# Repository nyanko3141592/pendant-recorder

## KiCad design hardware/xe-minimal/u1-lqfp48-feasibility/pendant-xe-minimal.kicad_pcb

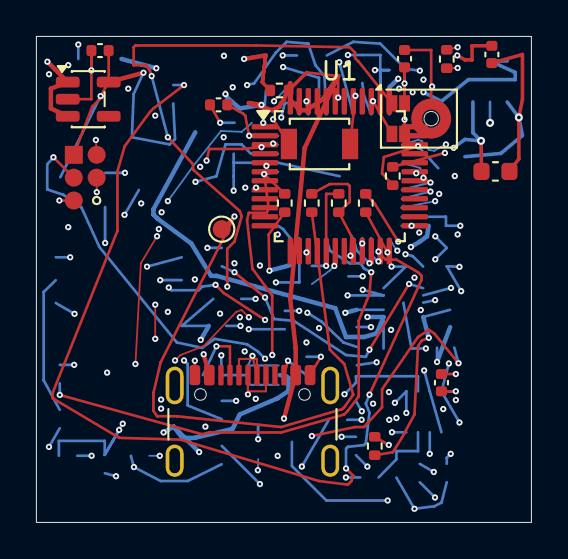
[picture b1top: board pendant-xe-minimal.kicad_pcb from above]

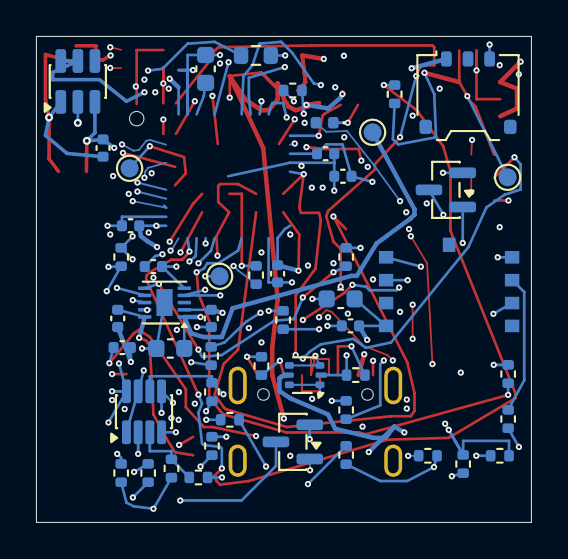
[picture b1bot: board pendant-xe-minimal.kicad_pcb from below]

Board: 6 copper layers, 27.5 x 27.0 mm, 71 parts (50 on the bottom side), 42 nets.

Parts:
C1, C2, C3, C6, C9, C22, C26: 100n; C_0402_1005Metric
C4: 10u; C_0603_1608Metric
C5: 4.7u; C_0603_1608Metric
C7, C16, C25: 1u; C_0402_1005Metric
C13: 2.2u 10V; C_0402_1005Metric
C14: 2.2u; C_0402_1005Metric
C15: 10u 10V effective >=1u; C_0603_1608Metric
C27: 4.7u effective TBD; C_0603_1608Metric
C28: 10n; C_0402_1005Metric
C29: 100n 10V; C_0402_1005Metric
C30: 50p 50V C0G; C_0402_1005Metric
D6: TJ-S1005SW4TGLC9Y-A5 amber LED; LED_0402_1005Metric
J1: USB4105-GF-A (candidate); USB_C_GCT_USB4105_GroundLand112
J2: Molex781710003 / DTP401525-XE; Molex_Pico-EZmate_78171-0003_1x03-1MP_P1.20mm_Vertical
J3: Factory SWD pogo candidate; SWD_Pogo_5Pad_P1.27mm
Q3, Q4: DMN63D8L-7; SOT-23
R1: 0R; R_0402_1005Metric
R2: 10k; R_0402_1005Metric
R3, R4, R13, R15, R22: 100k; R_0402_1005Metric
R6, R7: 5.1k 1%; R_0402_1005Metric
R10: 6.8k 1%; R_0402_1005Metric
R11, R39: 20k 1%; R_0402_1005Metric
R12, R36, R37, R38, R40: 100k 1%; R_0402_1005Metric
R14: 1M; R_0402_1005Metric
R21, R23: 22R tentative; R_0402_1005Metric
R24, R25, R28: 47k; R_0402_1005Metric
R32: 6.8k tentative; R_0402_1005Metric
R33, R34: 1M 1%; R_0402_1005Metric
R35: 10k 1%; R_0402_1005Metric
R41: 7.5k 1%; R_0402_1005Metric
R42: PTFR0402B24K0P9 24k 0.1%; R_0402_1005Metric
R43: 4.7k 1%; R_0402_1005Metric
R51: 0R 1%; R_0402_1005Metric
SW1: B3U-1000P (candidate); SW_SPST_B3U-1000P
TH1: NCU18XH103F60RB 10k 1% B3380; R_0603_1608Metric
TP1, TP2, TP3, TP5, TP6: TestPoint; TestPoint_Pad_D1.0mm
U1: STM32U585CIT6; LQFP-48_7x7mm_P0.5mm
U2: USBLC6-2P6; SOT-666
U3: BQ25185DLHR; Texas_DLH0010A_WSON-10-1EP_2.2x2mm_P0.4mm_EP0.9x1.5mm
U4: TPS7A0233PDBVR; SOT-23-5
U8: IM69D130V01; IM69D130_JLC_SMD_trial
U10: TPS22917DBVT; SOT-23-6
U11: CSNP32GCR01-BOW candidate; CSNP32GCR01_LGA8
U12: TLV7042DDFR; SOT-23-8

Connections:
/BAT: C14.1, J2.1, R33.1, TP1.1, U3.2
/BAT_ADC: C28.1, R33.2, R34.1, U1.11
/BAT_TS: R37.2, TH1.1, U12.2, U12.5
/BOOT0: R3.1, U1.44
/BUTTON_N: R4.2, SW1.1, U1.38
/CC1: J1.A5, R6.1
/CC2: J1.B5, R7.1
/CHARGER_TS: R35.1, U3.6
/CHG_ALLOW: R43.1, U1.20
/CHG_GUARD_GATE: Q4.1, R36.1, R43.2, U12.1, U12.7
/CHG_INHIBIT_GATE: Q4.3, R12.2, U3.4
/CHG_N: R11.2, U1.27, U3.9
/GND: C1.2, C2.2, C3.2, C4.2, C5.2, C6.2, C7.2, C9.2, C13.2, C14.2, C15.2, C16.2, C22.2, C25.2, C26.2, C27.2, C28.2, C29.2, C30.2, D6.1, J1.A1, J1.A12, J1.B1, J1.B12, J1.SH, J2.3, J3.5, Q3.2, Q4.2, R3.2, R6.2, R7.2, R10.2, R14.2, R22.2, R34.2, R35.2, R36.2, R39.2, R41.2, R42.2, SW1.2, TH1.2, TP6.1, U1.8, U1.23, U1.35, U1.47, U2.2, U3.5, U3.11, U4.2, U8.4, U8.5, U10.3, U11.4, U12.4
/ILIM_VSET: R42.1, U3.7
/ISET: C30.1, R10.1, U3.8
/NRST: C9.1, J3.3, R2.2, U1.7
/PDM_CLK: R21.2, U8.3
/PDM_CLK_MCU: R21.1, U1.39
/PDM_DATA: U1.40, U8.1
/SD_CLK: R23.2, U11.3
/SD_CLK_MCU: R23.1, U1.15
/SD_CS_N: R28.2, U1.14, U11.2
/SD_EN: R22.1, U1.41, U10.2
/SD_MISO: R25.2, U1.16, U11.6
/SD_MOSI: R24.2, U1.17, U11.5
/SD_V3: C26.1, C27.1, R24.1, R25.1, R28.1, TP5.1, U10.5, U10.6, U11.8
/STATUS_LED: R32.1, U1.29
/STATUS_LED_A: D6.2, R32.2
/SWCLK: J3.4, U1.37
/SWDIO: J3.2, U1.34
/SYS: C15.1, TP2.1, U3.1, U4.1, U4.3
/TS_COLD_REF: R38.2, R39.1, U12.3
/TS_HOT_REF: R40.2, R41.1, U12.6
/USB_DM: J1.A7, J1.B7, U1.32, U2.3, U2.4
/USB_DP: J1.A6, J1.B6, U1.33, U2.1, U2.6
/V3V3: C1.1, C2.1, C3.1, C4.1, C16.1, C22.1, C25.1, C29.1, J3.1, R1.1, R2.1, R4.1, R11.1, R15.1, R37.1, R38.1, R40.1, TP3.1, U1.1, U1.24, U1.36, U1.48, U4.5, U8.2, U10.1, U12.8
/VBUS: J1.A4, J1.A9, J1.B4, J1.B9, R13.1, R51.2, U2.5
/VBUS_CHARGER: C13.1, R12.1, R51.1, U3.10
/VBUS_GATE: Q3.1, R13.2, R14.1
/VBUS_N: Q3.3, R15.2, U1.10
/VCAP: C5.1, U1.22
/VDDA: C6.1, C7.1, R1.2, U1.9

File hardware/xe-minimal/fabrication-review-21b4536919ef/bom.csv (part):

Reference,Part/value,Footprint,Design note
U1,STM32U585CIU6,Package_DFN_QFN:QFN-48-1EP_7x7mm_P0.5mm_EP5.6x5.6mm,2MB Flash/786KB RAM; non-SMPS UFQFPN48. PB3/PB4 ADF AF3; PA5/6/7 SPI1 AF5. VDD USB shared 3.3V. JLC C5271026 Economic/Standard catalog match; ordinary stock and physical EVT pending.
C1,100n,Capacitor_SMD:C_0402_1005Metric,
C4,10u,Capacitor_SMD:C_0603_1608Metric,Main bulk capacitor; check startup and effective capacitance.
C9,100n,Capacitor_SMD:C_0402_1005Metric,
R2,10k,Resistor_SMD:R_0402_1005Metric,
J3,Factory SWD pogo pads,PendantMinimal:SWD_Pogo_5Pad_P1.27mm,Five exposed PCB pads; factory fixture required; VTref sense only. No assembly part and no buyer flashing.
SW1,B3U-1000P,Button_Switch_SMD:SW_SPST_B3U-1000P,JLC C231329 Economic/Standard catalog match; actuation and case-button EVT pending.
R4,100k,Resistor_SMD:R_0402_1005Metric,
J1,USB4105-GF-A,PendantD1:USB_C_GCT_USB4105_GroundLand112,JLC C3020560 Economic/Standard catalog match. Exact GCT land pattern and shield numbering audited; cable fit and high-difficulty assembly yield require EVT.
R6,5.1k 1%,Resistor_SMD:R_0402_1005Metric,
R7,5.1k 1%,Resistor_SMD:R_0402_1005Metric,
U2,USBLC6-2P6,Package_TO_SOT_SMD:SOT-666,"ST DS4260 SOT-666 pinout; JLC C15999 Economic/Standard catalog match. Orientation and land pattern are synchronized; USB ESD physical qualification pending."
C13,2.2u 10V,Capacitor_SMD:C_0402_1005Metric,
U3,BQ25185DLHR,Package_DFN_QFN:Texas_DLH0010A_WSON-10-1EP_2.2x2mm_P0.4mm_EP0.9x1.5mm,"BQ25185 Rev.B: R42=130k selects 4.1V nominal (4.1205V guaranteed maximum) and internal ILIM500; R10=30k gives 9..11mA fast charge. Upstream U13 TPS22950 with R51=20k bounds guaranteed total USB input to 66.06mA. Physical charge, transient, thermal and recovery qualification pending."
R10,RC0402FR-0730KL 30k 1%,Resistor_SMD:R_0402_1005Metric,"BQ25185 characterized 9..11mA fast charge at 30k; nominal termination 1.0mA and characterized upper 1.1mA. JLC C138008 stock 600357 observed 2026-10-28."
R11,20k 1%,Resistor_SMD:R_0402_1005Metric,
C14,2.2u,Capacitor_SMD:C_0402_1005Metric,
J2,Molex781710003 / DTP401525-XE,Connector_Molex:Molex_Pico-EZmate_78171-0003_1x03-1MP_P1.20mm_Vertical,"DTP401525-XE fixed pack: P1 red BAT+, P2 white built-in 10k NTC, P3 black GND. Pack NTC drives the independent hardware hot/cold charge-inhibit comparators directly. Exact R-T curve remains a receiving-inspection and EVT requirement; no user wiring."
R12,100k 1%,Resistor_SMD:R_0402_1005Metric,"YAGEO RC0402FR-07100KL; 100k 1%, +/-100ppm/C. Pulls U3 CE high from VBUS_LIMITED to inhibit charging when Q4 is off; no Q2 in this path."
C15,10u 10V effective >=1u,Capacitor_SMD:C_0603_1608Metric,SYS cap per TI; DC-bias capacitance must be qualified.
U4,TPS7A0233PDBVR,Package_TO_SOT_SMD:SOT-23-5,3.3V main rail: 48-pin MCU has no separate USB supply; dropout/capacity measurement required.
C16,1u,Capacitor_SMD:C_0402_1005Metric,
C31,1u 10V X5R,Capacitor_SMD:C_0402_1005Metric,TPS22950 VIN local bypass; placed adjacent to U13 per TI SLVSFJ2B section 10.3/10.4; effective capacitance and transient behavior require EVT.
C32,1u 10V X5R,Capacitor_SMD:C_0402_1005Metric,TPS22950 VOUT local bypass; placed directly below U13 with short filled-via connection; effective capacitance and transient behavior require EVT.
U8,IM69D130V01,Pendant:IM69D130_JLC_SMD_trial,"Direct 3.3V PDM, bottom port; no AAD. 0.768MHz/decimation48 candidate for 16kHz; acoustic validation required."
R21,22R tentative,Resistor_SMD:R_0402_1005Metric,
C22,100n,Capacitor_SMD:C_0402_1005Metric,
U10,TPS22917DBVT,Package_TO_SOT_SMD:SOT-23-6,"TPS22917DBVT load switch. CT is intentionally open for the TI-specified fastest turn-on; QOD is tied to SD_V3. Rise time, discharge and reverse-current behavior require EVT."
R22,100k,Resistor_SMD:R_0402_1005Metric,
C25,1u,Capacitor_SMD:C_0402_1005Metric,
R23,22R tentative,Resistor_SMD:R_0402_1005Metric,
R24,47k,Resistor_SMD:R_0402_1005Metric,
R25,47k,Resistor_SMD:R_0402_1005Metric,
R28,47k,Resistor_SMD:R_0402_1005Metric,
C26,100n,Capacitor_SMD:C_0402_1005Metric,
C27,4.7u,Capacitor_SMD:C_0603_1608Metric,HGC0603R7475K160NTHJ / C49333233 16 V X7R ±10% selected with C5; replaces non-orderable C6119855; voltage-bias and storage-inrush EVT pending.
TP1,TestPoint,TestPoint:TestPoint_Pad_D1.0mm,
TP2,TestPoint,TestPoint:TestPoint_Pad_D1.0mm,
TP3,TestPoint,TestPoint:TestPoint_Pad_D1.0mm,
TP5,TestPoint,TestPoint:TestPoint_Pad_D1.0mm,
TP6,TestPoint,TestPoint:TestPoint_Pad_D1.0mm,
R32,6.8k tentative,Resistor_SMD:R_0402_1005Metric,"LED current target 0.1-0.2mA; verify LED Vf, daylight readability and GPIO limits"
D6,TJ-S1005SW4TGLC9Y-A5 amber LED,LED_SMD:LED_0402_1005Metric,"Single status/battery indicator; JLC C273600 observed stock 6011 on 2026-10-28; firmware blinks on demand, normally dark."
C2,100n,Capacitor_SMD:C_0402_1005Metric,
C3,100n,Capacitor_SMD:C_0402_1005Metric,
C5,4.7u,Capacitor_SMD:C_0603_1608Metric,HGC0603R7475K160NTHJ / C49333233 16 V X7R ±10%; replaces non-orderable C6119855; VCAP effective-capacitance EVT pending.
C6,100n,Capacitor_SMD:C_0402_1005Metric,
C7,1u,Capacitor_SMD:C_0402_1005Metric,
R1,0R,Resistor_SMD:R_0402_1005Metric,
R3,100k,Resistor_SMD:R_0402_1005Metric,
Q3,DMN63D8L-7,Package_TO_SOT_SMD:SOT-23,"Diodes DMN63D8L-7 selected for engineering prototype VBUS presence detection; pin1 G pin2 S pin3 D. Temperature, detection and solder process qualification pending."
R13,100k,Resistor_SMD:R_0402_1005Metric,Purchase specification: YAGEO RC0402FR-07100KL; 0402; 1%; +/-100 ppm/C; 0.063 W at 70 C; 50 V working limit. Supplier SKU/price and circuit qualification pending.
R14,1M,Resistor_SMD:R_0402_1005Metric,Purchase specification: YAGEO RC0402FR-071ML; 0402; 1%; +/-100 ppm/C; 0.063 W at 70 C; 50 V working limit. Supplier SKU/price and circuit qualification pending.
R15,100k,Resistor_SMD:R_0402_1005Metric,Purchase specification: YAGEO RC0402FR-07100KL; 0402; 1%; +/-100 ppm/C; 0.063 W at 70 C; 50 V working limit. Supplier SKU/price and circuit qualification pending.
R33,1M 1%,Resistor_SMD:R_0402_1005Metric,"Battery divider 1:2; sample after settling, calibrate with VREFINT; not coulomb counting."
R34,1M 1%,Resistor_SMD:R_0402_1005Metric,"Battery divider 1:2; sample after settling, calibrate with VREFINT; not coulomb counting."
C28,10n,Capacitor_SMD:C_0402_1005Metric,"Battery divider 1:2; sample after settling, calibrate with VREFINT; not coulomb counting."
R35,10k 1%,Resistor_SMD:R_0402_1005Metric,Holds normal TS level when released; no floating TS/TTDM in intended circuit.
R36,100k 1%,Resistor_SMD:R_0402_1005Metric,"YAGEO RC0402FR-07100KL; 100k 1%, +/-100ppm/C. Reset/high-Z gate pulldown; no charging permission."
R37,100k 1%,Resistor_SMD:R_0402_1005Metric,Reduce thermistor excitation; 5.25V and99k gives52.99uA maximum branch current and69.60uW maximum thermistor power. Only powered from USB. Shared MCU rail for USB-independent temperature guard; BOR4 and startup timing qualification required.
R38,100k 1%,Resistor_SMD:R_0402_1005Metric, Shared MCU rail for USB-independent temperature guard; BOR4 and startup timing qualification required.
R39,20k 1%,Resistor_SMD:R_0402_1005Metric,Cold threshold candidate. Beta-model sensitivity is not full manufacturer R-T qualification. See temperature-screen.json.
R40,100k 1%,Resistor_SMD:R_0402_1005Metric, Shared MCU rail for USB-independent temperature guard; BOR4 and startup timing qualification required.
R41,7.5k 1%,Resistor_SMD:R_0402_1005Metric,Hot threshold candidate. Reserve margin for contact sensor lag; physical thermal qualification required.
U12,TLV7042DDFR,Package_TO_SOT_SMD:SOT-23-8,"TLV7042 open-drain wired-AND temperature permission. Either fault pulls Q4 gate low. BAT_TS is driven by the fixed pack's internal 10k NTC; comparator tolerance, pack R-T lot spread, startup and installed thermal lag require EVT."
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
